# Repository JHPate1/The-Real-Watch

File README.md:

# The-Real-Watch
> A watch that ACTUALLY tracks your health by monitoring your surroundings and constantly monitoring for active threats.

---

## What is it and how is it different??

Let me start from the drawing board. I've noticed EXPENSIVE Garmin, Apple and Fitbits that don't even do their real job. Like for example, your health isn't just your BPM, O2 and Pedometer levels. It's more than that. My watch includes ALL those AND a environmental sensor, because the real influencing force is the environment you're in, not how much you walk. This watch constantly scans for CO2, Gas, Noise, Pressure, Noise levels and more! This watch is also capable of running APPs that runs via bluetooth and wifi. It can be used to communicate with other watches eg; if you're hiking and your friend has the same watch. You can communicate with them in realtime like a walkie talkie. This watch isnt just any watch, Its a watch that breaks feats that were never imaginable. Imagine being able to view your bank balance all from your watch that has a ESP32 inside of it!
This is indeed a very ambitious venture but I AM confident I have what it takes.

---

## BOM

*(Tarrifs are gonna kill this project, smh)*

| Item | Cost |
|------|------|
| PCB + 3D Printing (PCBWay, Cheaper than JLCPCB) | $157.90 |
| PCBWay Balance | -$25.00 |
| Coupons | -$8.00 |
| 3D printing | -$24.90 |
| **PCBWay Total** | **$100.00** |
| | |
| 8 Ohm Small Speakers | $8.45 |
| Mini Vibration Motors | $5.99 |
| 3.7V 500mAh 603030 Lipo Battery Rechargeable Lithium Polymer ion Battery Pack | $6.99 |
| waveshare 1.28inch Round LCD Display Module with Touch Panel | $25.99 |
| Amazon Tax | $2.52 |
| **Amazon Total** | **$49.94** |
| | |
| **Project TOTAL** | **$149.94** |

> **Tariffs and shipping are likely to be decided later, or the prices may go down.**

---

## What about the software?

The software is already in development! I am making the internal code first as I dont know how the screen will behave.

---

## Pictures

(Render by my friend in blender, does not have github so I will update this Readme once he does.)

(Yes I use tinkercad, so what? My laptop doesn't even run cloud services like onshape efficiently, and this was before I was notified of the deadline extension.)

## Special thanks

Outpost by HackClub! (Bro this is my 40th project im submitting, this time with EVERYTHING. I've worked 30 HOURS and MY MENTAL HEALTH off of this project, so PLEASE approve this for funding. I even selected the CHEAPEST components for this project, the tarrifs aren't even my fault)

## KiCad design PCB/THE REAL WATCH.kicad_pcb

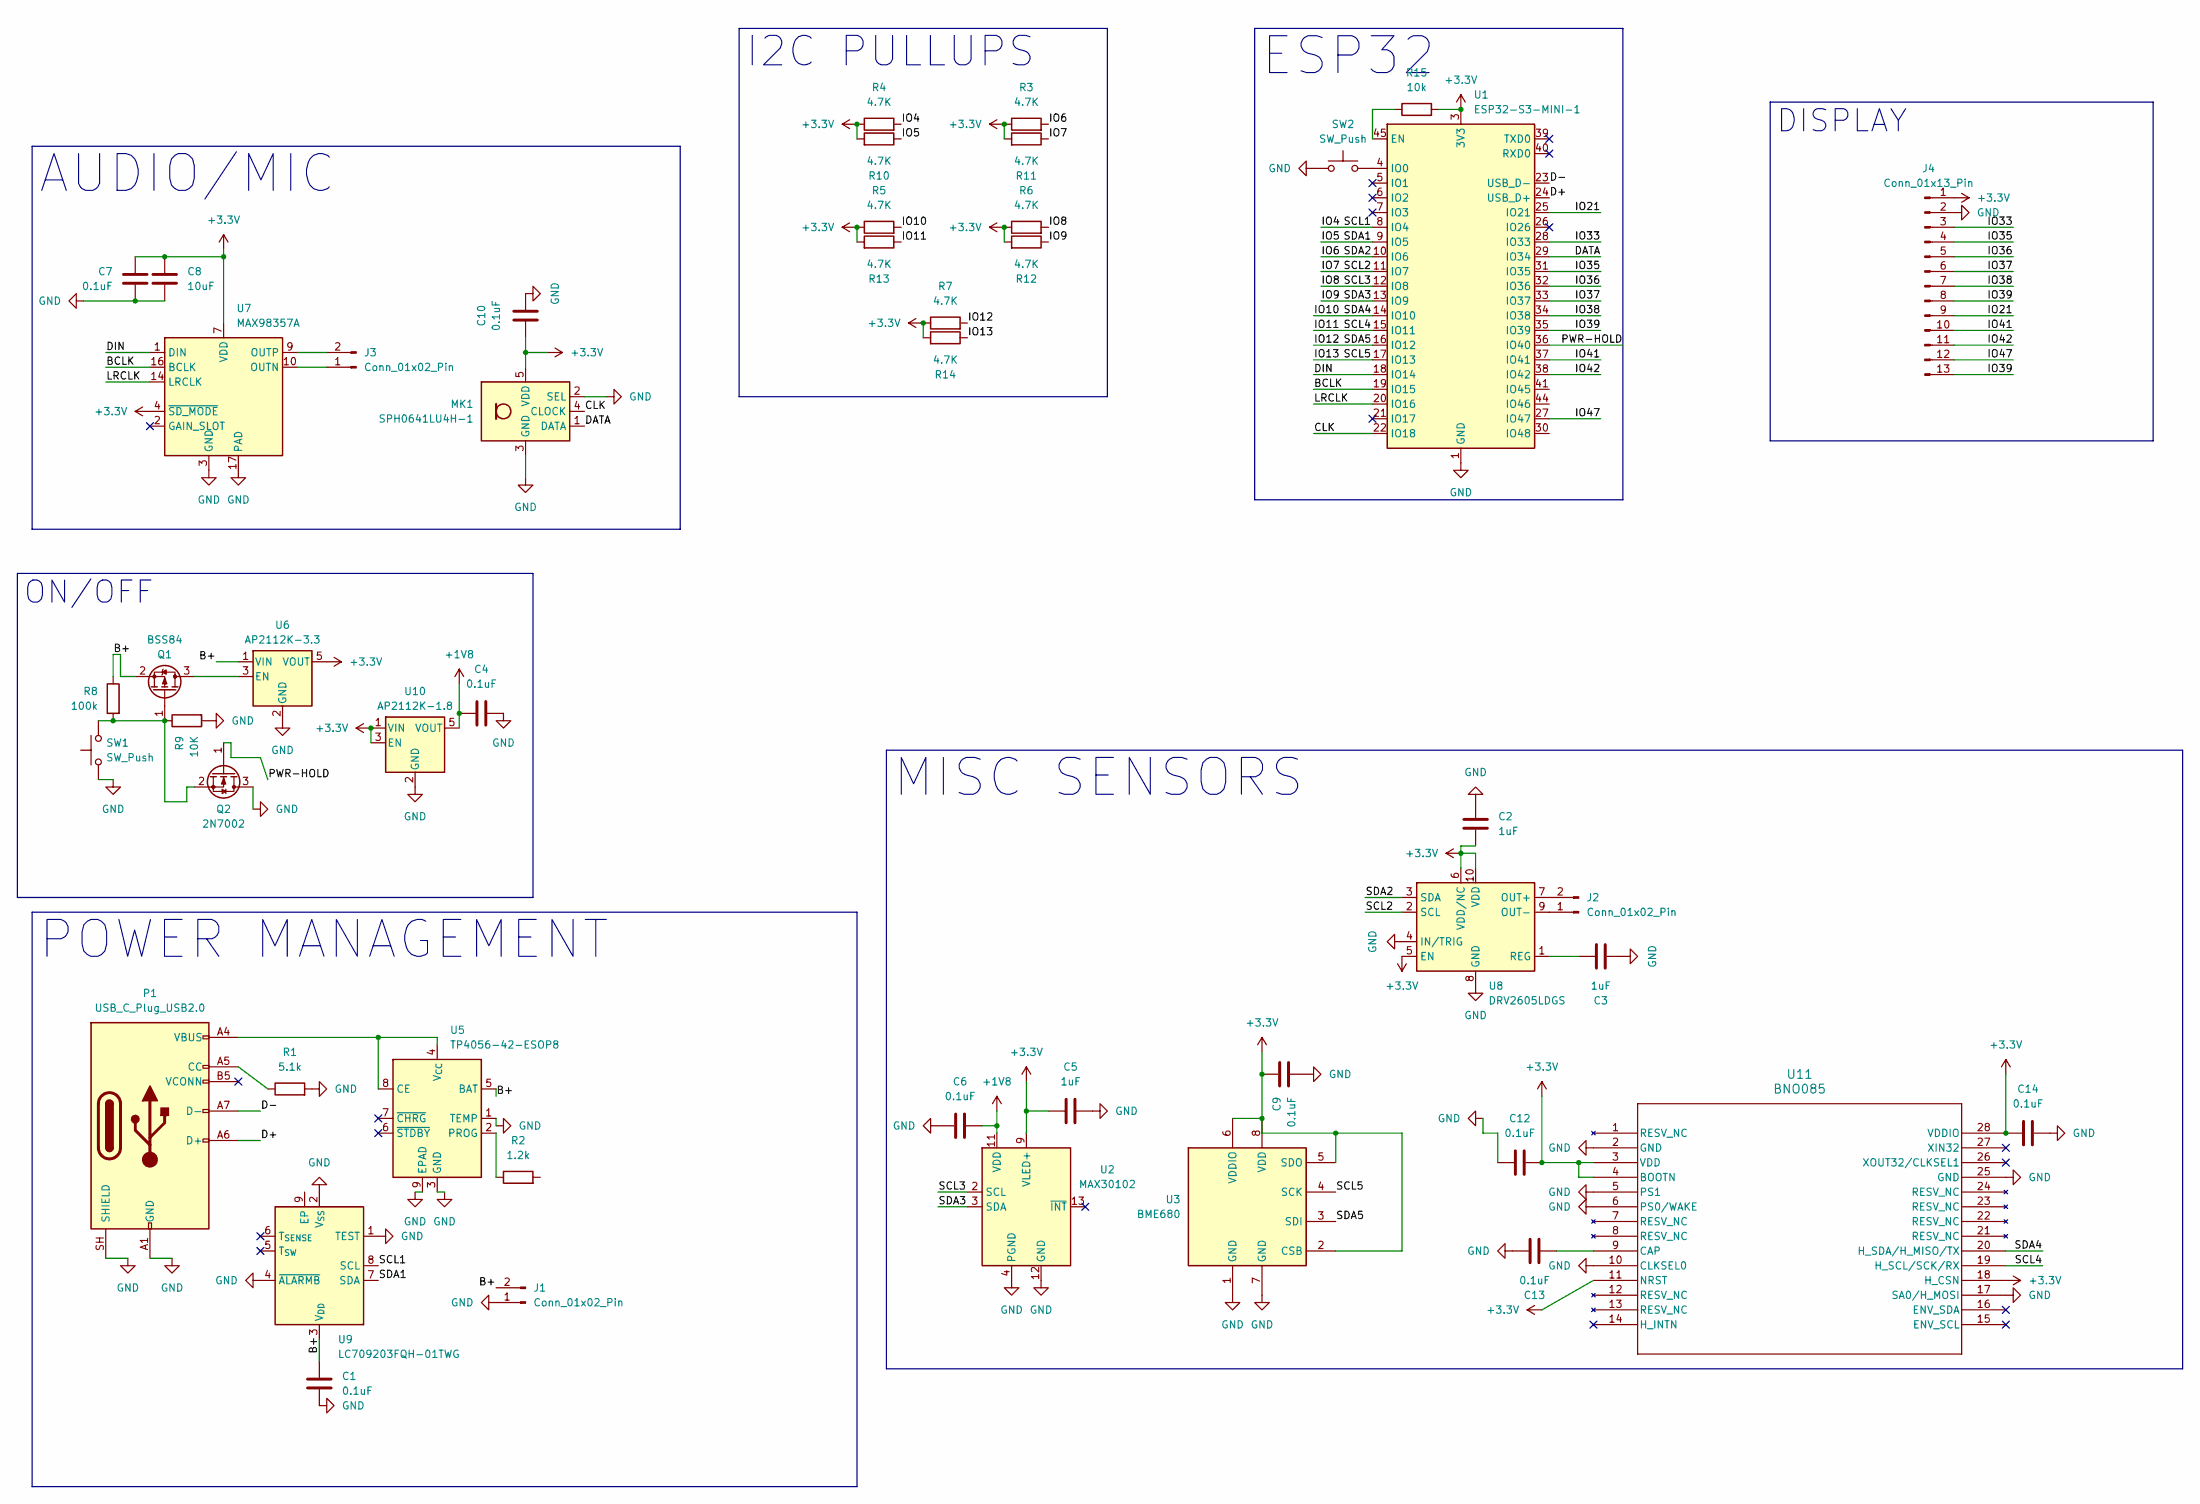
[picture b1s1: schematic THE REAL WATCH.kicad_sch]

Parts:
C1, C4, C6, C7, C9, C10, C12, C13, C14: 0.1uF; C_0603_1608Metric
C2, C3, C5: 1uF; C_0603_1608Metric
C8: 10uF; C_0603_1608Metric
J1, J2, J3: Conn_01x02_Pin; PinHeader_1x02_P1.00mm_Vertical
J4: Conn_01x13_Pin; PinHeader_1x13_P1.00mm_Vertical
MK1: SPH0641LU4H-1; Knowles_LGA-5_3.5x2.65mm
P1: USB_C_Plug_USB2.0; USB_C_Receptacle_Amphenol_124019772112A
Q1: BSS84; SOT-23
Q2: 2N7002; SOT-23
R1: 5.1k; R_0603_1608Metric
R2: 1.2k; R_0603_1608Metric
R3, R4, R5, R6, R7, R10, R11, R12, R13, R14: 4.7K; R_0603_1608Metric
R8: 100k; R_0603_1608Metric
R9: 10K; R_0603_1608Metric
R15: 10k; R_0603_1608Metric
SW1: SW_Push; Panasonic_EVQPUJ_EVQPUA
SW2: SW_Push; SW_Push_1P1T_NO_CK_KMR2
U1: ESP32-S3-MINI-1; ESP32-S2-MINI-1
U2: MAX30102; Maxim_OLGA-14_3.3x5.6mm_P0.8mm
U3: BME680; Bosch_LGA-8_3x3mm_P0.8mm_ClockwisePinNumbering
U5: TP4056-42-ESOP8; WSON-14-1EP_4.0x4.0mm_P0.5mm_EP2.6x2.6mm
U6: AP2112K-3.3; SOT-23-5
U7: MAX98357A; TQFN-16-1EP_3x3mm_P0.5mm_EP1.23x1.23mm
U8: DRV2605LDGS; TSSOP-10_3x3mm_P0.5mm
U9: LC709203FQH-01TWG; WDFN-8-1EP_4x3mm_P0.65mm_EP2.4x1.8mm
U10: AP2112K-1.8; SOT-23-5
U11: BNO085; LGA-28_CEV

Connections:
+1V8: C4.1, C6.1, U2.11 (VDD), U10.5 (VOUT)
+3.3V: C2.2, C5.2, C7.1, C8.1, C9.1, C10.1, C12.1, C14.1, J4.1, MK1.5 (VDD), R3.1, R4.1, R5.1, R6.1, R7.1, R10.2, R11.2, R12.2, R13.2, R14.2, R15.2, U1.3 (3V3), U2.9 (VLED+), U2.10 (VLED+), U3.2 (CSB), U3.5 (SDO), U3.6 (VDDIO), U3.8 (VDD), U6.5 (VOUT), U7.4 (~SD_MODE), U7.7 (VDD), U7.8 (VDD), U8.5 (EN), U8.6 (VDD/NC), U8.10 (VDD), U10.1 (VIN), U10.3 (EN), U11.3 (VDD), U11.4 (BOOTN), U11.11 (NRST), U11.18 (H_CSN), U11.28 (VDDIO)
/B+: C1.1, J1.2, Q1.2 (S), R8.1, U5.5 (BAT), U6.1 (VIN), U9.3 (V_{DD})
/BCLK: U1.19 (IO15), U7.16 (BCLK)
/CLK: MK1.4 (CLOCK), U1.22 (IO18)
/D+: P1.A6 (D+), U1.24 (USB_D+)
/D-: P1.A7 (D-), U1.23 (USB_D-)
/DATA: MK1.1 (DATA), U1.29 (IO34)
/DIN: U1.18 (IO14), U7.1 (DIN)
/IO4: R4.2, U1.8 (IO4), U9.8 (SCL)
/IO5: R10.1, U1.9 (IO5), U9.7 (SDA)
/IO6: R3.2, U1.10 (IO6), U8.3 (SDA)
/IO7: R11.1, U1.11 (IO7), U8.2 (SCL)
/IO8: R6.2, U1.12 (IO8), U2.2 (SCL)
/IO9: R12.1, U1.13 (IO9), U2.3 (SDA)
/IO10: R5.2, U1.14 (IO10), U11.20 (H_SDA/H_MISO/TX)
/IO11: R13.1, U1.15 (IO11), U11.19 (H_SCL/SCK/RX)
/IO12: R7.2, U1.16 (IO12), U3.3 (SDI)
/IO13: R14.1, U1.17 (IO13), U3.4 (SCK)
/IO21: J4.9, U1.25 (IO21)
/IO33: J4.3, U1.28 (IO33)
/IO35: J4.4, U1.31 (IO35)
/IO36: J4.5, U1.32 (IO36)
/IO37: J4.6, U1.33 (IO37)
/IO38: J4.7, U1.34 (IO38)
/IO39: J4.8, J4.13, U1.35 (IO39)
/IO41: J4.10, U1.37 (IO41)
/IO42: J4.11, U1.38 (IO42)
/IO47: J4.12, U1.27 (IO47)
/LRCLK: U1.20 (IO16), U7.14 (LRCLK)
/PWR-HOLD: Q2.1 (G), U1.36 (IO40)
GND: C1.2, C2.1, C3.2, C4.2, C5.1, C6.2, C7.2, C8.2, C9.2, C10.2, C12.2, C13.2, C14.2, J1.1, J4.2, MK1.2 (SEL), MK1.3 (GND), P1.A1 (GND), P1.A12 (GND), P1.B1 (GND), P1.B12 (GND), P1.SH (SHIELD), Q2.3 (D), R1.2, R9.2, SW1.1, SW2.1, U1.1 (GND), U1.2 (GND), U1.42 (GND), U1.43 (GND), U1.46 (GND), U1.47 (GND), U1.48 (GND), U1.49 (GND), U1.50 (GND), U1.51 (GND), U1.52 (GND), U1.53 (GND), U1.54 (GND), U1.55 (GND), U1.56 (GND), U1.57 (GND), U1.58 (GND), U1.59 (GND), U1.60 (GND), U1.61 (GND), U1.62 (GND), U1.63 (GND), U1.64 (GND), U1.65 (GND), U2.4 (PGND), U2.12 (GND), U3.1 (GND), U3.7 (GND), U5.1 (TEMP), U5.3 (GND), U5.9 (EPAD), U6.2 (GND), U7.3 (GND), U7.11 (GND), U7.15 (GND), U7.17 (PAD), U8.4 (IN/TRIG), U8.8 (GND), U9.1 (TEST), U9.2 (V_{SS}), U9.4 (~ALARMB), U10.2 (GND), U11.2 (GND), U11.5 (PS1), U11.6 (PS0/WAKE), U11.10 (CLKSEL0), U11.17 (SA0/H_MOSI), U11.25 (GND)
unnamed: J2.1, U8.9 (OUT-)
unnamed: J2.2, U8.7 (OUT+)
unnamed: J3.1, U7.10 (OUTN)
unnamed: J3.2, U7.9 (OUTP)
unnamed: P1.A5 (CC), R1.1
unnamed: Q1.3 (D), U6.3 (EN)
unnamed: Q1.1 (G), Q2.2 (S), R8.2, R9.1, SW1.2
unnamed: R15.1, U1.45 (EN)
unnamed: SW2.2, U1.4 (IO0)
unnamed: P1.A4 (VBUS), P1.A9 (VBUS), P1.B4 (VBUS), P1.B9 (VBUS), U5.4 (V_{CC}), U5.8 (CE)
unnamed: R2.1, U5.2 (PROG)
unnamed: C3.1, U8.1 (REG)
unnamed: C13.1, U11.9 (CAP)

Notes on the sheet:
DISPLAY
MISC SENSORS
ESP32
I2C PULLUPS
ON/OFF
POWER MANAGEMENT
AUDIO/MIC

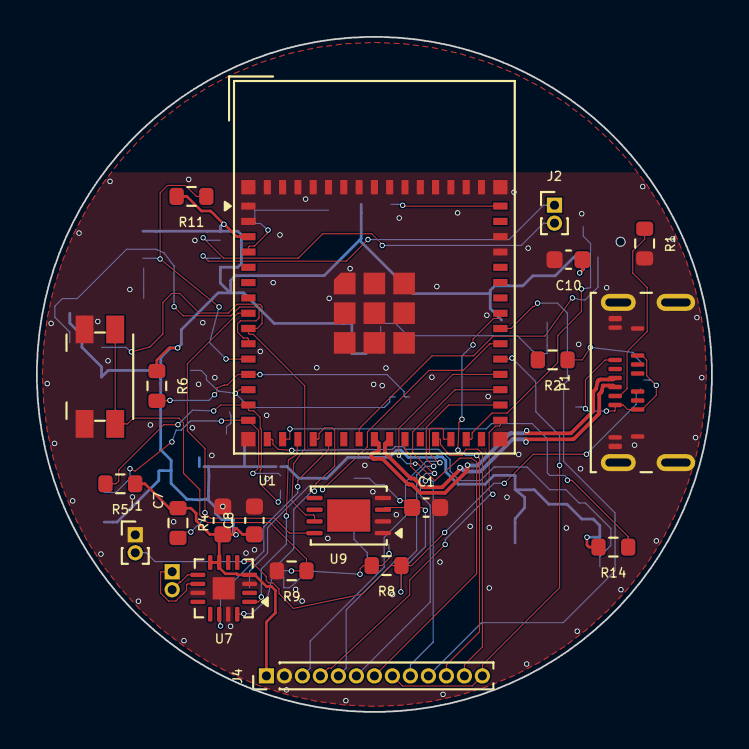
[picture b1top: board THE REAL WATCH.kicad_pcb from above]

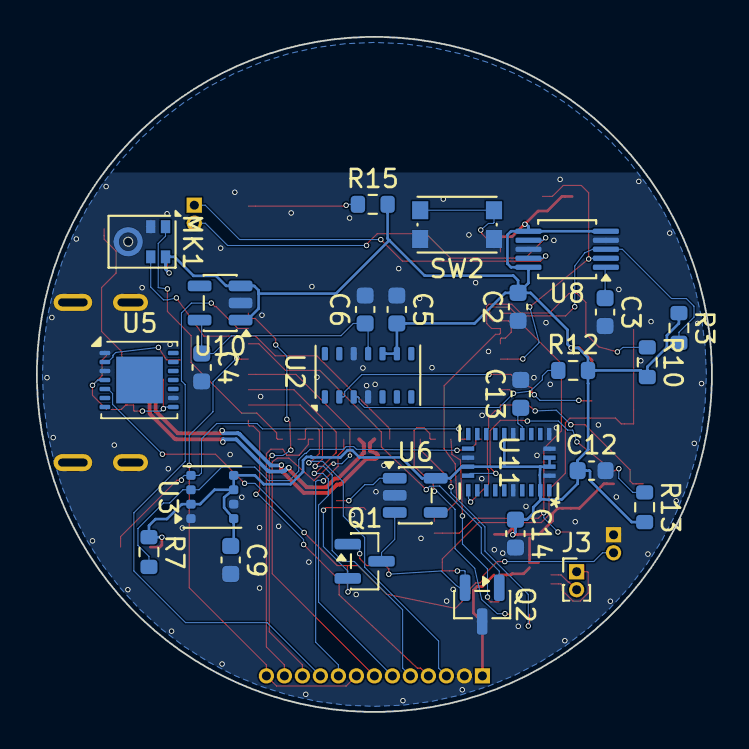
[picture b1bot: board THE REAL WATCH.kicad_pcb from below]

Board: 2 copper layers, 37.5 x 37.5 mm, 48 parts (27 on the bottom side), 45 nets.
